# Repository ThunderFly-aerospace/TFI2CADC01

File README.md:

# TFI2CADC01 — I²C 16‑bit ADC for UAVs

Compact 4‑channel analog‑to‑digital converter module for Pixhawk‑class autopilots and ThunderFly form‑factor carrier boards. Based on [TI ADS1115 (16‑bit Σ‑Δ ADC)](https://www.ti.com/lit/ds/symlink/ads1115.pdf?ts=1741234332539). Dual Pixhawk JST‑GH I²C ports support in‑line daisy‑chaining.

## Key features

* 4 × single‑ended inputs (AIN0…AIN3) up to VDD range (0–3.3 V)
* 16‑bit ADC (ADS1115IDGS) with programmable gain amplifier (PGA)
* I²C interface, 100/400 kHz compliant; on‑board 4.7 kΩ pull‑ups to 3.3 V
* ADDR solder-bridge for selectable I²C address (default 0x48)
* ALERT/RDY interrupt output (optional test‑point)
* Bus‑powered from +5 V; on‑board LDO to internal 3.3 V
* Input/rail protection and status LEDs (PWR, activity)
* Two JST‑GH 4‑pin I²C ports for Pixhawk; one 2×4 header for access to analog inputs and ground

## Electrical

* **Input supply (JST‑GH VBUS):** 5.4 V (Pixhawk I²C standard)
* **I²C levels:** 3.3 V (pull‑ups on board)
* **Analog input range:** 0…3.3 V (referenced to GND)
* **ESD / surge:** front‑end and bus clamped (5.6 V TVS on 5 V)

> ⚠️ Do **not** exceed 3.3 V on AINx relative to GND.

## Connectors & pinout

### JST‑GH I²C (J2, J3) — Pixhawk standard

```
Pin 1: VBUS +5V
Pin 2: SCL
Pin 3: SDA
Pin 4: GND
```

Both ports are wired in parallel for pass‑through/daisy‑chain.

### I²C addressing

Default assembly is 0x48.

| ADDR input  | 7‑bit I²C address |
| ----------- | ----------------- |
| GND         | 0x48 (default)    |
| VDD (3.3 V) | 0x49              |
| SDA         | 0x4A              |
| SCL         | 0x4B              |

> The board provides pads/jumper position for changing the address. See silkscreen near ADDR.

## Jumpers / test points

* **T1 (ALERT/RDY):** routes the ALERT/RDY pin to a test pad for optional host interrupt. Leave open if unused.
* **JP2/JP2:** board address option tie (factory) to 3.3 V.

## LEDs

* **PWR (green):** 3.3 V power rail present.
* **ACT (orange):** activity/diagnostic (wired to logic as per schematic option).

## Typical wiring (Pixhawk)

1. Plug either JST‑GH port to a Pixhawk I2C port (5 V provided by autopilot).
2. Daisy‑chain additional I²C node from the second JST‑GH if needed.
3. Connect sensors to AIN0…AIN3 via J1, or wire your signals to the corresponding pads.
4. (Optional) Strap ADDR and solder for a non‑default address if multiple TFI2CADC01 are present on the same I2C bus.

## Software notes (ADS1115)

* **PX4 support:** PX4 Autopilot includes a native driver for ADS1115 (16‑bit, up to 860 SPS, 4‑channel delta‑sigma ADC with PGA, oscillator, internal VREF, comparator and I²C). See [PX4 driver](https://github.com/PX4/PX4-Autopilot/tree/main/src/drivers/adc/ads1115) and [TI ADS1115](https://www.ti.com/product/ADS1115).
* **Use cases:** Pixhawk‑compatible ADC module is suitable for prototyping/attaching analog‑output sensors (e.g., temperature, humidity, gas presence, etc.).
* **Configuration tips:** configure PGA for expected full‑scale to maximize resolution; for single‑ended reads use MUX AIN0/1/2/3 vs GND; to minimize I²C polling enable comparator in "traditional" mode and read **ALERT/RDY** (if T1 is wired).

### Example (Linux `i2c-tools`)

```bash
# Detect
sudo i2cdetect -y 1

# Read a register (conversion register 0x00)
sudo i2cget -y 1 0x48 0x00 w
```

## Mechanical & form factor

PCB follows the **ThunderFly form factor** for avionics modules (mounting & stacking compatible with TF carriers). Two JST‑GH side‑by‑side for easy in‑line installation inside UAV wiring harnesses.

## Revision history

  - TFI2CADC01A - Initial revision

## Availability and Customization

The TFI2CADC01 is available from ThunderFly s.r.o. For a commercial quotation, contact us at [sale@thunderfly.cz](mailto:sale@thunderfly.cz) or shop via our Lectronz or Tindie store.

We also offer application‑specific modifications on request. Typical options include alternative input scaling (dividers/shunts), connector or cable variations, pre‑strapped I²C addresses, and simple mounting adaptations. Basic changes are usually provided at no additional cost with an estimated lead time of approximately three weeks.

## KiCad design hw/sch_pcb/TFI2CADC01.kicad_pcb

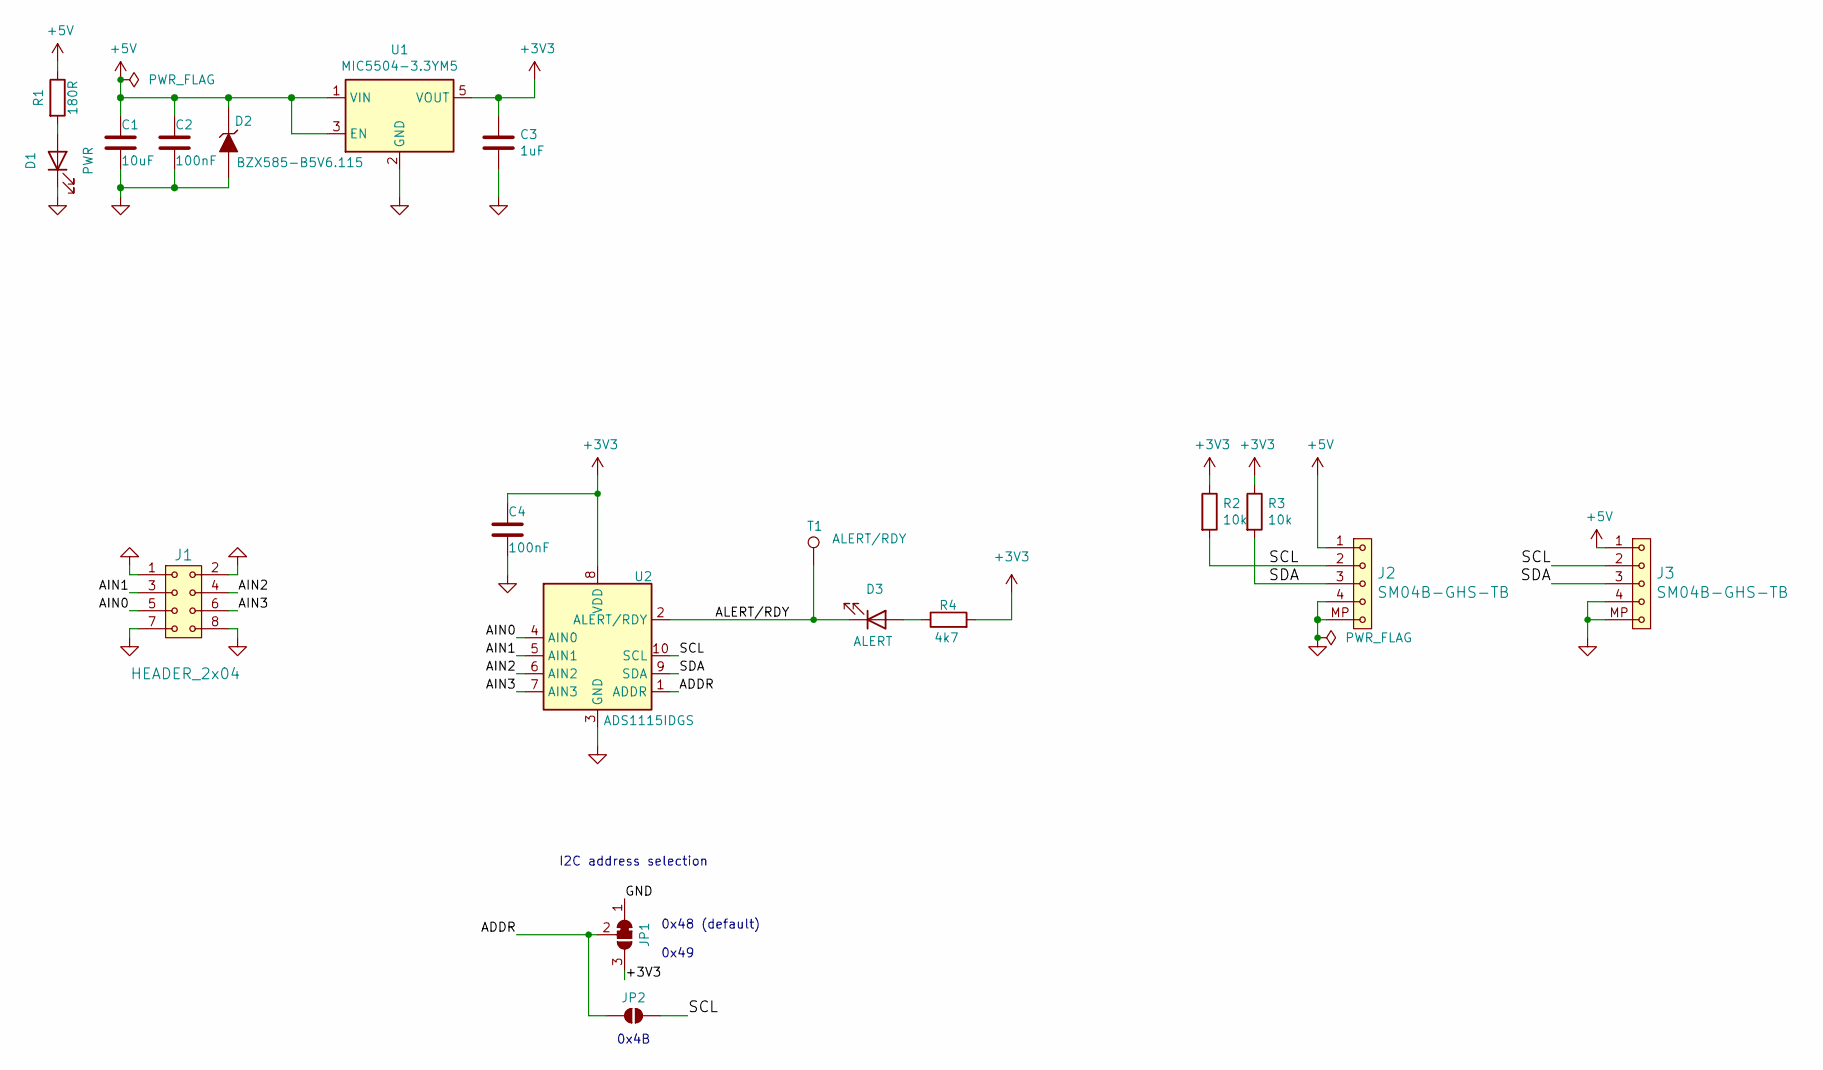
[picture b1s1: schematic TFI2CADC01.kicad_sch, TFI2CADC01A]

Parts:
C1: 10uF; C_0805_2012Metric
C2, C4: 100nF; C_0603_1608Metric
C3: 1uF; C_0603_1608Metric
D1: PWR; LED_0603_1608Metric
D2: BZX585-B5V6.115; D_SOD-523
D3: ALERT; LED_0603_1608Metric
J1: HEADER_2x04; PinHeader_2x04_P2.54mm_Edge_Mount
J2, J3: SM04B-GHS-TB; JST_GH_SM04B-GHS-TB_1x04-1MP_P1.25mm_Horizontal
JP1: SolderJumper-3_P1.3mm_Bridged12_RoundedPad1.0x1.5mm
JP2: SolderJumper_2_Open; SolderJumper-2_P1.3mm_Open_RoundedPad1.0x1.5mm
R1: 180R; R_0603_1608Metric
R2, R3: 10k; R_0603_1608Metric
R4: 4k7; R_0603_1608Metric
T1: ALERT/RDY; TestPoint_Pad_D2.0mm
U1: MIC5504-3.3YM5; SOT-23-5
U2: ADS1115IDGS; VSSOP-10_3x3mm_P0.5mm

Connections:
+3V3: C3.1, C4.1, JP1.3 (B), R2.1, R3.1, R4.2, U1.5 (VOUT), U2.8 (VDD)
+5V: C1.1, C2.1, D2.1 (K), J2.1, J3.1, R1.1, U1.1 (VIN), U1.3 (EN)
/ADDR: JP1.2 (C), JP2.1 (A), U2.1 (ADDR)
/AIN0: J1.5, U2.4 (AIN0)
/AIN1: J1.3, U2.5 (AIN1)
/AIN2: J1.4, U2.6 (AIN2)
/AIN3: J1.6, U2.7 (AIN3)
/ALERT/RDY: D3.1 (K), T1.1, U2.2 (ALERT/RDY)
/SCL: J2.2, J3.2, JP2.2 (B), R2.2, U2.10 (SCL)
/SDA: J2.3, J3.3, R3.2, U2.9 (SDA)
GND: C1.2, C2.2, C3.2, C4.2, D1.1 (K), D2.2 (A), J1.1, J1.2, J1.7, J1.8, J2.4, J2.MP, J3.4, J3.MP, JP1.1 (A), U1.2 (GND), U2.3 (GND)
unnamed: D1.2 (A), R1.2
unnamed: D3.2 (A), R4.1

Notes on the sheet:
0x48 (default)
I2C address selection
0x4B
0x49

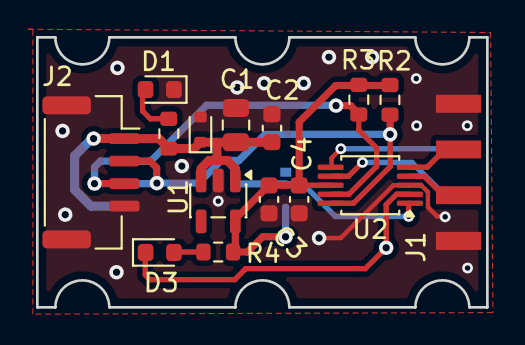
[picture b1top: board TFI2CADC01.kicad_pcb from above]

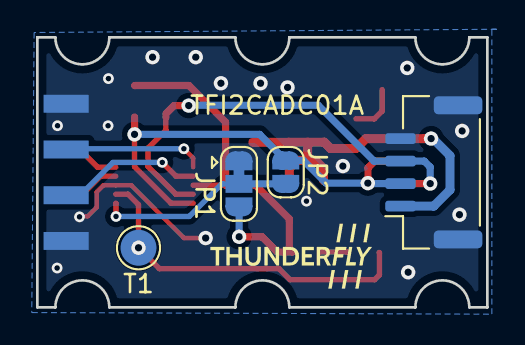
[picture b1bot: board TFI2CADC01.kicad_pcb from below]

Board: 2 copper layers, 25.0 x 15.0 mm, 19 parts (4 on the bottom side), 13 nets.

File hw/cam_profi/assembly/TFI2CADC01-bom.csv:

Component,Description,Part,References,Value,Footprint,Quantity Per PCB,Datasheet,ust_id
1,Unpolarized capacitor,C,C2C4,100nF,C_0603_1608Metric,2,~,5c70984812875079b91f8bf2
2,Unpolarized capacitor,C,C3,1uF,C_0603_1608Metric,1,~,5c70984812875079b91f8bc2
3,Unpolarized capacitor,C,C1,10uF,C_0805_2012Metric,1,~,5c70984812875079b91f8bbd
4,Light emitting diode,LED,D3,ALERT,LED_0603_1608Metric,1,~,60d581db1287500165f859a2
5,,D_ZENER,D2,BZX585-B5V6.115,D_SOD-523,1,,60879d38128750769ee58e48
6,Light emitting diode,LED,D1,PWR,LED_0603_1608Metric,1,~,60d582331287500165f859d0
7,2x04 2.54 mm pitch header,HEADER_2x04,J1,HEADER_2x04,PinHeader_2x04_P2.54mm_Edge_Mount,1,,
8,,SM04B-GHS-TB,J2J3,SM04B-GHS-TB,JST_GH_SM04B-GHS-TB_1x04-1MP_P1.25mm_Horizontal,2,,5c86273d1287500b4e0280be
9,Resistor,R,R1,180R,R_0603_1608Metric,1,~,5c70984512875079b91f8957
10,Resistor,R,R4,4k7,R_0603_1608Metric,1,~,5c70984512875079b91f8962
11,Resistor,R,R2R3,10k,R_0603_1608Metric,2,~,5c70984512875079b91f8962
12,"Ultra-Small, Low-Power, I2C-Compatible, 860-SPS, 16-Bit ADCs With Internal Reference, Oscillator, and Programmable Comparator, VSSOP-10",ADS1115IDGS,U2,ADS1115IDGS,VSSOP-10_3x3mm_P0.5mm,1,http://www.ti.com/lit/ds/symlink/ads1113.pdf,6934a81dea235ce78ba25ac5
13,"300mA Low-dropout Voltage Regulator, Vout 3.3V, Vin up to 5.5V, SOT-23",MIC5504-3.3YM5,U1,MIC5504-3.3YM5,SOT-23-5,1,http://ww1.microchip.com/downloads/en/DeviceDoc/MIC550X.pdf,5c7255e81287500b4e112ea2

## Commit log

2025-09-26 Initial design for modification.
2025-09-26 Cleanup and activate workflows.
2025-09-26 Update actions products
2025-09-26 Initial plan
2025-09-27 Update workflow files
2025-10-01 Hotové schéma - otázka jumpery a konektory na vstupu
2025-10-02 ADS1115 obvod s headry
2025-10-02 Adding address selection
2025-10-02 Updating footprints
2025-10-02 Updating schematics
2025-10-02 Add testpoint to Alert pin.
2025-10-11 Adding pcb
2025-10-11 Improve layout.
2025-10-13 Updating pcb
2025-10-15 Improve silkscreen.
2025-10-15 Improve documentation.
2025-12-06 Improve layout. Fix DRC and ERC errors. Improve PinHeader edge-mount footprint. Update footprints.
2025-12-06 Improve footprint selection. Fix layout Documentation update.
2025-12-25 Add PCB dimensions.
2026-02-15 Automatic update of KiCAD outputs
